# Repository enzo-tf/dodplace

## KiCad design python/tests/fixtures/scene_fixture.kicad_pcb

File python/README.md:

# dodplace — Python front end

Turns a KiCad board into the engine's IR (`scene.bin`, see `../ir/spec.md`).
The C engine never sees a KiCad file, a PDF or an HTTP response.

```
board.kicad_pcb ──► extract (JSON) ──► enrich (phase 3) ──► scene.bin ──► dodplace-solve
```

## See also

[`../docs/data-map.md`](../docs/data-map.md) - every artifact the project
writes, which file each field lands in, and the diagrams.

## Running

```sh
uv sync --extra dev --extra pdf --extra ipc   # 88 MB; skip `step` unless you want OCCT
uv run dodplace info                          # which KiCad python and solver are visible

uv run dodplace ingest BOARD.kicad_pcb -o scene.bin --report report.json
uv run dodplace show scene.bin
uv run dodplace solve scene.bin -o placement.bin
uv run dodplace enrich skeleton BOARD.kicad_pcb    # parts CSV to fill in
uv run dodplace enrich extra BOARD.kicad_pcb       # commented rules starter

uv run pytest                                 # 160 tests, most of them without KiCad
```

`dodplace info` reports the interpreter and solver the CLI would use.

The solver itself lives in C (`../src/solver*.c`) and is documented stage by
stage in `../docs/data-map.md` §4b: semantic clustering, force-directed global
placement, simulated annealing, then MTV legalisation. Its own tests are
`../tests/test_solver.c` (run by `ctest`).

> `uv sync --extra X` **replaces** the extra set, so always list the extras you
> want together. `--all-extras` also installs OCCT + VTK (~850 MB), which the
> STEP provider does **not** need.

## KiCad plugin

Two actions in the PCB editor, both **read-only** — they never modify the board
file:

| Action | What it does |
|---|---|
| `dodplace: analyze board` | full pipeline, writes the scene and the reports into `<board>/.dodplace/`, validates with the C engine |
| `dodplace: report only` | the same analysis without writing anything but the log |

Both run the same shim; the second passes `--report-only`, which the shim
forwards from the manifest's `args`.

### Test it from a terminal first

The action and the command line run exactly the same code, so you can iterate
without restarting KiCad:

```sh
uv run dodplace plugin analyze --board path/to/board.kicad_pcb
uv run dodplace plugin analyze --ipc            # the board open in KiCad
uv run dodplace plugin analyze --ipc --save     # save it through KiCad first
uv run dodplace plugin analyze --ipc --report-only   # write nothing but the log
```

Output looks like this:

```
board: /…/board.kicad_pcb
  found via: explicit
  4 components, 14 pins, 6 nets (12 connections)
  enrichment: 0 part(s), 0 datasheet(s), 0 cached, 4 STEP model(s)
  coverage: height 4/4, mass 0/4, orientation 0/4, pin roles 0/14, pin current 0/14
  constraints: 2 decoupling
  degraded (0x0002007E): NO_MASS NO_ROTATION_DATA NO_PIN_ELEC NO_PIN_CURRENT …
  engine validation: ok (exit 0)
  unresolved: mass_g 4/4, orientation_deg 4/4, power_w 4/4, r_theta_ja 4/4
  artifacts: /…/.dodplace
```

The `unresolved` line is the actionable part: it names the optional fields no
source could supply, with how many components or pins they affect, so you know
exactly what to add to `extra.toml`, a parts file or a datasheets directory.

Exit codes: `0` fine, `1` pipeline or validation failure, `2` usage, `3` no
board found (KiCad closed and no `--board`).

### Install it into KiCad

```sh
uv run dodplace plugin install     # writes ~/Documents/KiCad/<version>/plugins/dodplace/
uv run dodplace plugin status      # install state, repo check, IPC reachability
uv run dodplace plugin uninstall   # removes only that directory
```

Restart KiCad afterwards; the action appears in the PCB editor toolbar (and in
the plugin list of the preferences dialog). The first launch makes KiCad create
a virtualenv for the plugin, which takes a moment.

`install` writes four things: `plugin.json`, a generated `main.py` shim, a
**`requirements.txt`**, and a one-line pointer file at `~/.config/dodplace/repo`. The shim is stdlib-only and
Python 3.9 compatible because KiCad runs it with **its own** interpreter; it
relays the call to this checkout's interpreter, using absolute paths baked in at
install time (a process started by KiCad from the Finder has no shell `PATH`).
The pointer file is the escape hatch if you move the checkout: edit it or
re-run `install`.

### Three traps found the hard way

The first two produce the same symptom — a plugin that loads cleanly in the
trace and no button anywhere — and neither prints an error. The third makes the
action fail the moment it runs.

**1. A missing `requirements.txt`.** KiCad's plugin manager runs
`pip install -r requirements.txt` in the plugin directory at startup and marks
the plugin **ready only when that succeeds**
(`common/api/api_plugin_manager.cpp`). Without the file the job fails and the
action is never registered; because the virtual environment already exists,
every later start repeats the same failing job.

dodplace ships a comment-only `requirements.txt`: the shim is stdlib-only and
the real dependencies live in the project's uv environment, so nothing needs to
be installed and no network access is required.

**2. A button with no bitmap.** `show-button: true` only creates a toolbar
entry; the bitmap comes exclusively from `icons-light` / `icons-dark`
(`common/api/api_plugin.cpp`), and with neither declared the button is blank.
The icons are generated by `tools/make_plugin_icons.py` (pure standard library)
and shipped as package data.

The installer verifies both before writing anything: it refuses a plugin whose
requirements would install packages, a button with no icon, and an icon declared
in the manifest but not shipped.

**3. KiCad's environment poisons a nested interpreter.** Before running an
action, KiCad exports `PYTHONHOME` and `PYTHONPATH` pointing at *its* bundled
Python 3.9. Our shim starts the project's Python 3.12, which inherits them,
looks for its standard library inside KiCad's 3.9 tree and dies with
`Fatal Python error: init_fs_encoding … No module named 'encodings'`.

The shim therefore runs the child with `-E` (ignore `PYTHON*` variables) *and*
strips `PYTHONHOME`, `PYTHONPATH`, `PYTHONSTARTUP`, `PYTHONEXECUTABLE`,
`PYTHONNOUSERSITE` and `VIRTUAL_ENV` from its environment. Guarded by a test
that reproduces KiCad's exact variables.

### The requirements.txt trap

KiCad's plugin manager runs `pip install -r requirements.txt` in the plugin
directory at startup and marks the plugin **ready only when that succeeds**
(`common/api/api_plugin_manager.cpp`). A plugin without that file is never
registered: no error dialog, no action, just silence — and because the virtual
environment already exists, every later start repeats the same failing job.

### Seeing the output

KiCad shows the action's stdout/stderr in its message panel (10.0.1+). For a
terminal, the same summary is appended to a log next to the board:

```sh
uv run dodplace plugin log --board path/to/board.kicad_pcb
uv run dodplace plugin log -f                 # follows the nearest log
```

### The action does not appear

1. `uv run dodplace plugin status` — it reports whether the plugin is installed,
   whether the three files KiCad needs are all present, whether the baked repo
   path still resolves, whether the venv answers, and whether the IPC socket is
   reachable. Shim-level failures also land in `~/.cache/dodplace/shim.log`.
2. Ask KiCad why. Quit it completely first — launching the binary while an
   instance runs only activates the existing window, so the trace never reaches
   the real process:

   ```sh
   pgrep -fl kicad || echo "fully quit"
   KICAD_ENABLE_WXTRACE=1 WXTRACE=KICAD_API /Applications/KiCad/KiCad.app/Contents/MacOS/kicad
   ```

   The lines that matter are `Manager: installing dependencies for …` and
   `Manager: marking <identifier> as ready`. The first without the second means
   the dependency job failed — almost always a missing or unusable
   `requirements.txt`.
3. **The action runs but exits 1** with `No module named 'encodings'` in the
   trace: the nested-interpreter environment problem above. Re-run
   `dodplace plugin install`; the shim is regenerated with the fix.
4. **"no board from the IPC API"** in a terminal run: `KiCad.get_board()` uses
   the `GetOpenDocuments` command, which only has a handler while the **PCB
   editor** is open with a board loaded. `plugin status` says which case you are
   in — *not reachable*, *no open board*, or a board path. The action itself runs
   from the PCB editor, so it never hits this.
5. `iCCP: known incorrect sRGB profile` and similar lines are libpng noise from
   KiCad's own icons. They mean nothing about the plugin.
6. macOS may ask to let KiCad control **System Events** right after an action
   runs. That is KiCad bringing its own window back to the front
   (`osascript -e 'tell application "System Events" … set the frontmost …'`),
   not the plugin; denying it is harmless.

### Why the action does not place anything yet

Applying a placement needs two things that are not finished: the bottom-side
orientation convention has to be verified with a real round trip through the IPC
API (see the note below), and the write-back must happen as a single undoable
commit. Until then the action deliberately cannot write to the board.

## Extraction backend

Extraction uses **KiCad's own `pcbnew` module, headless**, via the bundled
interpreter (3.9 on macOS, first `python3` with `pcbnew` elsewhere; override
with `DODPLACE_KICAD_PYTHON`). The extractor (`kicad/pcbnew_extract.py`) is
stdlib-only, so it never needs this project's dependencies, and only JSON
crosses the interpreter boundary.

**Why not the IPC API for reading?** Measured against KiCad 10.0.5:

| Need | IPC (kipy) | pcbnew |
|---|---|---|
| Chained board outline | only `BoardSegment`s on `Edge.Cuts`, arcs included | `GetBoardPolygonOutlines()` |
| Courtyard polygon | only `BoardSegment`s in the definition | `GetCourtyard()` |
| Pad size | buried in `padstack` per layer | `pad.GetSize()` |
| Layer by name | no server-side handler in 10.0.5 | not needed |
| Requires a running GUI | yes (KiCad 9/10) | no |

Reimplementing segment chaining over IPC is exactly the format drift the IPC
API exists to avoid, and it would gain nothing. IPC is used where only it can
help: in phase 4 the plugin saves the open board and **applies** the resulting
placement live, as one undoable commit.

## Extract document schema

The contract between board readers and `to_scene`:

```jsonc
{
  "schema": "dodplace.extract/1",
  "backend": "pcbnew", "backend_version": "10.0.5",
  "board":  { "path": "...", "copper_layers": 4, "outline": [[[x, y], ...]] },
  "keepouts": [ { "name": "...", "layer_mask": 3, "xy": [[[x, y], ...]] } ],
  "netclasses": [ { "name": "Default", "clearance_mm": 0.2, "track_width_mm": 0.25 } ],
  "nets": [ { "name": "GND", "netclass": "Default" } ],
  "components": [ {
      "ref": "U1", "value": "MCU", "fpid": "Pkg:QFN",
      "x": 10.0, "y": 10.0, "rot_deg": 90.0, "side": "top", "locked": false,
      "courtyard": [ [[x, y], ...] ],          // footprint-local mm, may be empty
      "pads": [ { "number": "1", "net": "GND", "x": -1.0, "y": -1.0,
                  "size_x": 0.5, "size_y": 0.5, "attrib": "smd", "drill": 0.0 } ]
  } ],
  "warnings": []
}
```

`x`/`y` for pads are **footprint-local and unrotated**, which is exactly what
`PIN_OFFSET_X`/`PIN_OFFSET_Y` want. The extractor verifies its own rotation
frame on every pad (`board = origin + R(theta) * local`) and reports a warning
rather than emitting wrong data.

## Responsibilities

The producer resolves what it can and marks what it could not, so the engine's
fallbacks are never implemented twice. See `../ir/spec.md` §6 and §8 for the
split, and `to_scene.py` for the exact list this front end raises.

## Enrichment

Optional data is resolved by a precedence chain, strongest first:

```
extra.toml  >  parts file  >  board  >  netlist heuristic  >  datasheet PDF  >  STEP model
```

Sources are *additive*: each fills what the previous ones left empty, and the
winner of every field is recorded. Whatever stays unresolved is left absent on
purpose, so the C engine applies its documented fallback and raises the matching
`DEGRADED_*` bit - no fallback is implemented twice.

| Source | Command | What it provides |
|---|---|---|
| `extra.toml` | `enrich extra BOARD` writes a starter; auto-detected next to the board | locked parts, fixed orientations, symmetry, thermal envelopes, decoupling targets, keepouts, ceiling, airflow, per-net clearance |
| parts file | `enrich skeleton BOARD` writes one to fill in; `enrich parts FILE` imports it; auto-imported next to the board | LCSC/MPN, height, mass, power, datasheet link, per-pad current/role |
| netlist heuristic | on by default, `--no-heuristics` to skip | pairs every capacitor with the ICs sharing its power net |
| datasheet PDF | `ingest --datasheets DIR --rules RULES` | height, power, Rθ, currents, extracted by rules with a confidence and a page number |
| STEP model | on by default, `--no-step` to skip | part height from the board's own 3D model references, no OCCT needed |
| name convention | on by default | height from `-H2.8` in a model or footprint name, **low confidence**, only when nothing measurable exists |

### Two starters instead of a blank page

```sh
uv run dodplace enrich extra    BOARD.kicad_pcb   # -> extra.toml next to the board
uv run dodplace enrich skeleton BOARD.kicad_pcb   # -> dodplace-parts.csv, one row per supplier code
```

`enrich extra` reads the board and seeds the rules that are obvious from it:
mechanical parts to lock (`H*`, `FID*`, `J*`), dissipating candidates (`U`, `Q`,
`L`, `CE`) with their part values in a comment, and a commented example of
everything else. Nothing is imposed: the file is valid and safe as generated.

`enrich skeleton` writes one CSV row per supplier part number found on the
board, with the identity columns filled and `Height (mm)`, `Mass (g)`,
`Power (W)` and `Datasheet` empty. One real board needed **14 rows for 536
components**. Both files are auto-discovered on the next run: the parts file is
imported into the store, the rules file is applied.

`[[component]]` selectors accept globs (`ref = "FID*"`, `fpid = "Tuile_LED:*"`),
and later blocks win field by field, so a family rule can be refined by a
specific one.

`extra.example.toml` at the repo root documents every user-rule knob, and
`src/dodplace/enrich/rules/*.toml` holds the shipped datasheet rules.

### Cache and report

The cache is a directory of JSON records, one file per key, sharded two levels
deep and written atomically. No SQL and nothing opaque - you can read, grep and
delete any record, and a corrupt one is treated as a miss:

```
<board>/.dodplace/cache/parts/<ab>/<sha256>.json       # lcsc:C25804, mpn:..., fp:...
<board>/.dodplace/cache/datasheets/<ab>/<sha256>.json   # keyed by content hash
```

The store never holds a PDF or a STEP file, only the facts extracted from them
(with source, confidence and timestamp). Point it elsewhere with
`--store DIR`, share it between projects, or skip it with `--no-store`.
`dodplace enrich show --store DIR` lists what is cached.

Two reports come out of a run:

* `--report FILE` - counts, coverage, constraints and the degraded categories.
* `--enrich-report FILE` - per component and per field: the value used, the
  source that won, its confidence, or `{"unresolved": true}`. This is the file
  to read when a placement looks odd, and the place to look for what to add to
  `extra.toml`.

### What enrichment cannot fix

Some bits are *irreducible* by design and always reported: `NO_NET_WEIGHTS`
(nothing carries net priority), `NO_MAX_LENGTH` and `NO_SEGREGATION` (no data
model yet in the engine), and `COURTYARD_BBOX` for parts without an exact
courtyard on the board.

## Tests

| File | Covers |
|---|---|
| `test_writer.py` | IR encode/decode, **byte-identical** round trip of the C golden fixture, builder validation |
| `test_naming.py` | net-name electrical inference, differential pair matching |
| `test_to_scene.py` | extract → scene: counts, flags, matrix, degraded bits (no KiCad) |
| `test_extract.py` | the frozen extract of the fixture board; live pcbnew comparison when available |
| `test_enrich.py` | store, every provider, precedence, coverage bits, PDF end to end |
| `test_pipeline.py` | extract → scene.bin → the C solver → placement.bin → numpy |
| `test_plugin.py` | manifest schema, installer in a temp dir, shim relay and 3.9 syntax, the analyze action |

`tests/fixtures/scene_fixture.kicad_pcb` is generated by
`tests/fixtures/make_fixture_board.py` (run under KiCad's interpreter) and
`scene_fixture.extract.json` is its frozen extract, so most tests run without
KiCad installed. The PDF test builds a valid PDF in memory; only the
`pcbnew`-backed tests and the official-model test skip when KiCad is absent.

## Known issue to settle in phase 4

The local frame is `board = origin + R(theta) * local`, verified pad by pad
against KiCad for both sides (`test_extract.py` relies on that check having
produced no warnings). Bottom-side parts come back from KiCad with a mirrored
orientation (`C1` in the fixture is at 180 degrees after a flip), so **when the
plugin writes orientations back through the IPC API, the bottom-side
orientation convention must be verified with a real round trip** before the
placement is applied. Until that is done, the plugin should treat the two sides
separately and report any mismatch rather than saving.

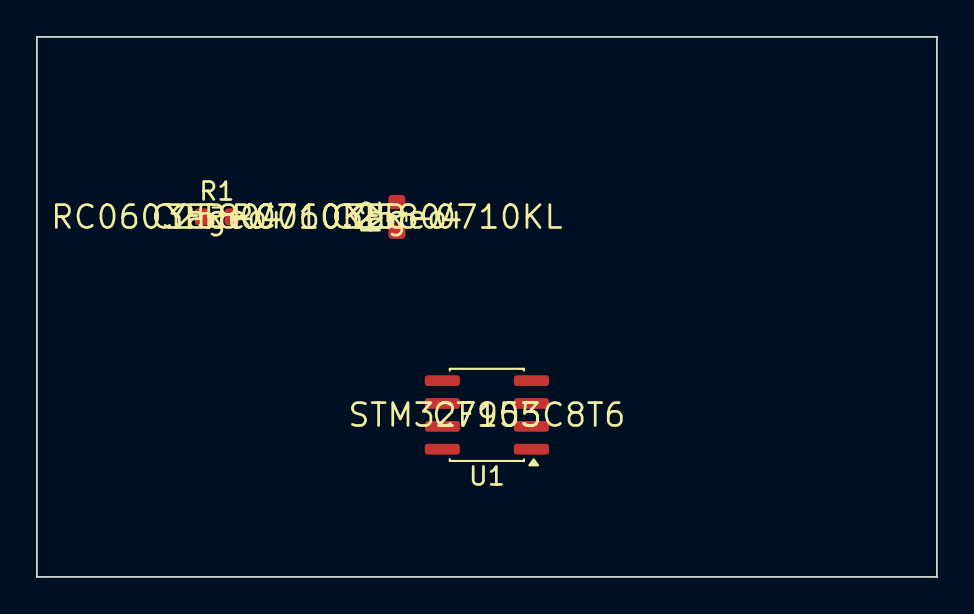
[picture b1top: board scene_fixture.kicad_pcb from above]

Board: 2 copper layers, 50.0 x 30.0 mm, 4 parts (1 on the bottom side), 3 nets, no tracks yet.

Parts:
C1: C_0603_1608Metric
R1, R2: R_0603_1608Metric
U1: SOIC-8_3.9x4.9mm_P1.27mm

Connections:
GND: C1.2, R1.2, R2.2, U1.4
USB1_P: R2.1, U1.1
VCC: C1.1, R1.1, U1.8
